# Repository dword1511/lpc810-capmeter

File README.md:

LPC810-based Capacitance Meter
==============================

Pros:

* Dual-speed measurement
* Auto-ranging
* 1pF to 9999.99uF
* Reasonable precision after stray capacitance subtracted
* Calibration-free for C > 1nF if precision resistors used
* UART output (115200 8N1)
* Compact
* Affordable
* Single-chip, low component count
* SMD-free, prototype-board-friendly layout
* Only uses common components
* Microcontroller can be flashed via UART

Cons:

* May get affected by ESR and leakage
* Measuring frequency not controllable
* 1% error in clock introduced by the microcontroller
* Require relatively new arm-none-eabi toolchain for reasonable binary size
* Time-constant-based approach is not as precise as LCR bridge
* Requires 3.3V power supply

Refs:

* [Capacitance Meter and RC Time Constants](http://www.arduino.cc/en/Tutorial/CapacitanceMeter)
* [Getting Started with the LPC810](https://learn.adafruit.com/getting-started-with-the-lpc810/introduction)
* [LPC810 CodeBase](https://github.com/microbuilder/LPC810_CodeBase)
* [lpc21isp](http://sourceforge.net/projects/lpc21isp/)
* [GNU Tools for ARM Embedded Processors](https://launchpad.net/gcc-arm-embedded) **(If code size is too big, try this toolchain)**
* [LPCXpresso Sample Code Bundle for the LPC8xx](http://www.lpcware.com/content/nxpfile/lpcxpresso-sample-code-bundle-lpc8xx)
* [NXP Switch Matrix Tool for LPC81x](http://www.lpcware.com/content/nxpfile/nxp-switch-matrix-tool-lpc800)
* [A smarter way to write micros()](http://micromouseusa.com/?p=296)

Compiling:
    cd src && make && make flash
Use `CROSS=/path/to/toolchain-` and `COMPORT=/dev/ttyACM0` to change toolchain / serial used for flashing.

[OSH Park](https://oshpark.com/shared_projects/58C6wB6e)

Pin Assignment:

         +---v---+
    TXD -|1     8|- VREF
    RXD -|2     7|- GND
    IO3 -|3     6|- 3V3
    IO2 -|4     5|- VCAP
         +-------+

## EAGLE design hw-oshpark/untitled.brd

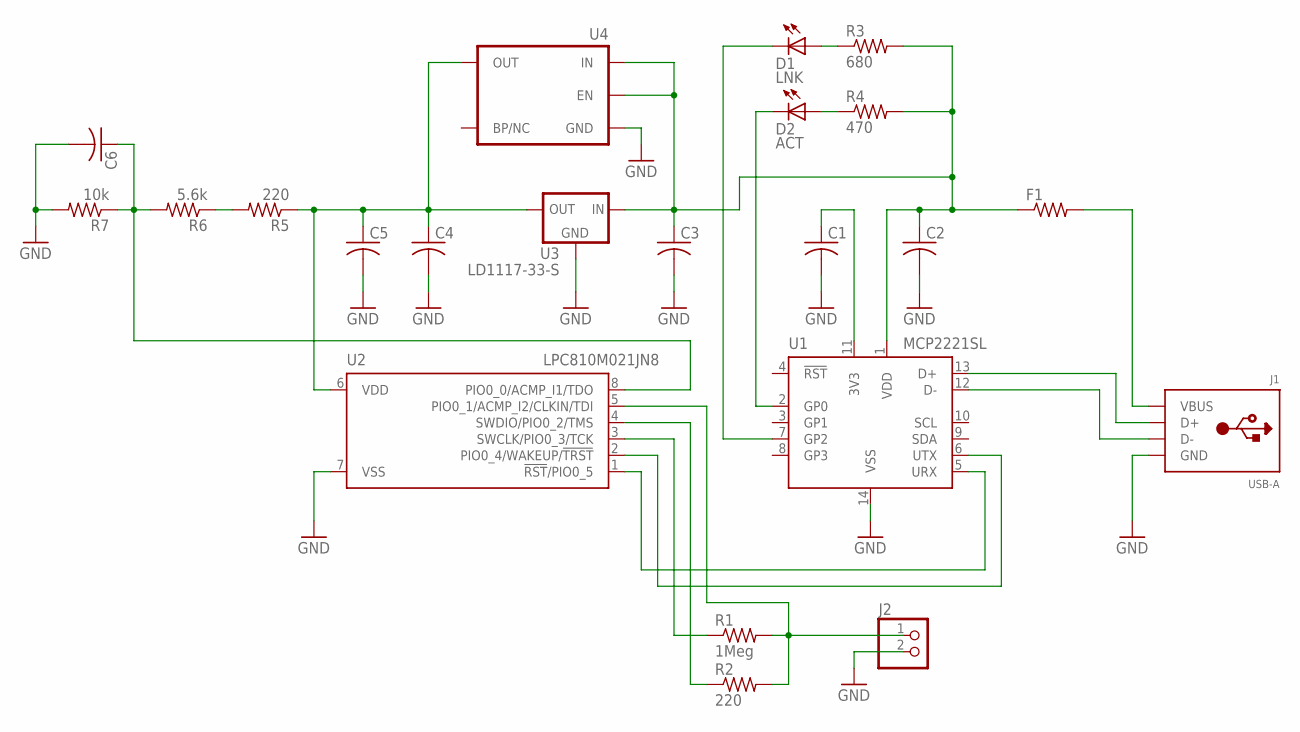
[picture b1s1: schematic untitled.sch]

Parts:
C1, C2, C3, C4, C5, C6: C-USC0805; C0805
D1: LNK; SML0805
D2: ACT; SML0805
F1: R-US_R0805; R0805
J1: USB-A; MOLEX_480371000
J2: PINHD-1X2; 1X02
R1: 1Meg; R0805
R2, R5: 220; R0805
R3: 680; R0805
R4: 470; R0805
R6: 5.6k; R0805
R7: 10k; R0805
U1: MCP2221SL; SOIC-14
U2: LPC810M021JN8; DIP-8
U3: LD1117-33-S; SOT-223
U4: LDO-SOT23-5; SOT-23-5

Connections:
GND: C1.2, C2.2, C3.2, C4.2, C5.2, C6.2, J1.4 (GND), J2.2, R7.2, U1.14 (VSS), U2.7 (VSS), U3.1 (GND), U4.2 (GND)
unnamed: F1.2, J1.1 (VBUS)
unnamed: D2.C, U1.2 (GP0)
unnamed: C1.1, U1.11 (3V3)
unnamed: J1.3 (D+), U1.13 (D+)
unnamed: J1.2 (D-), U1.12 (D-)
unnamed: U1.5 (URX), U2.1 (!RST!/PIO0_5)
unnamed: U1.6 (UTX), U2.2 (PIO0_4/WAKEUP/!TRST!)
unnamed: R1.1, U2.3 (SWCLK/PIO0_3/TCK)
unnamed: R2.1, U2.4 (SWDIO/PIO0_2/TMS)
unnamed: J2.1, R1.2, R2.2, U2.5 (PIO0_1/ACMP_I2/CLKIN/TDI)
unnamed: D1.C, U1.7 (GP2)
unnamed: D2.A, R4.1
unnamed: D1.A, R3.1
unnamed: C6.1, R6.2, R7.1, U2.8 (PIO0_0/ACMP_I1/TDO)
unnamed: R5.2, R6.1
unnamed: C2.1, C3.1, F1.1, R3.2, R4.2, U1.1 (VDD), U3.3 (IN), U4.1 (IN), U4.3 (EN)
OUT: C4.1, C5.1, R5.1, U2.6 (VDD), U3.2 (OUT), U3.4 (OUT), U4.5 (OUT)

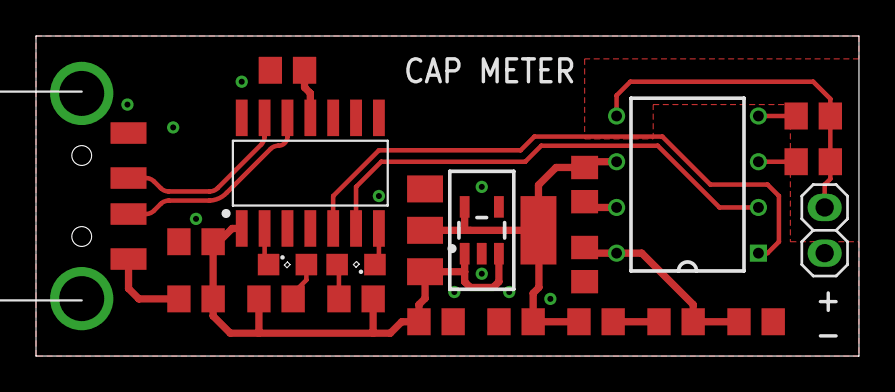
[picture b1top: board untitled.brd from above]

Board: 2 copper layers, 45.7 x 17.8 mm, 22 parts (0 on the bottom side), 18 nets.

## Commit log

2015-05-02 init
2015-05-02 hardware
2015-05-02 first working version
2015-05-03 revise pcb
2015-05-03 cleanning up and add docs
2017-01-29 commit old doc changes
2017-01-29 maintaince for new gcc
2017-02-04 eagle design file (slightly newer than oshpark version)
2017-03-21 move old hw to hw-proto
2017-03-21 update Makefile
2017-03-21 small fixes
